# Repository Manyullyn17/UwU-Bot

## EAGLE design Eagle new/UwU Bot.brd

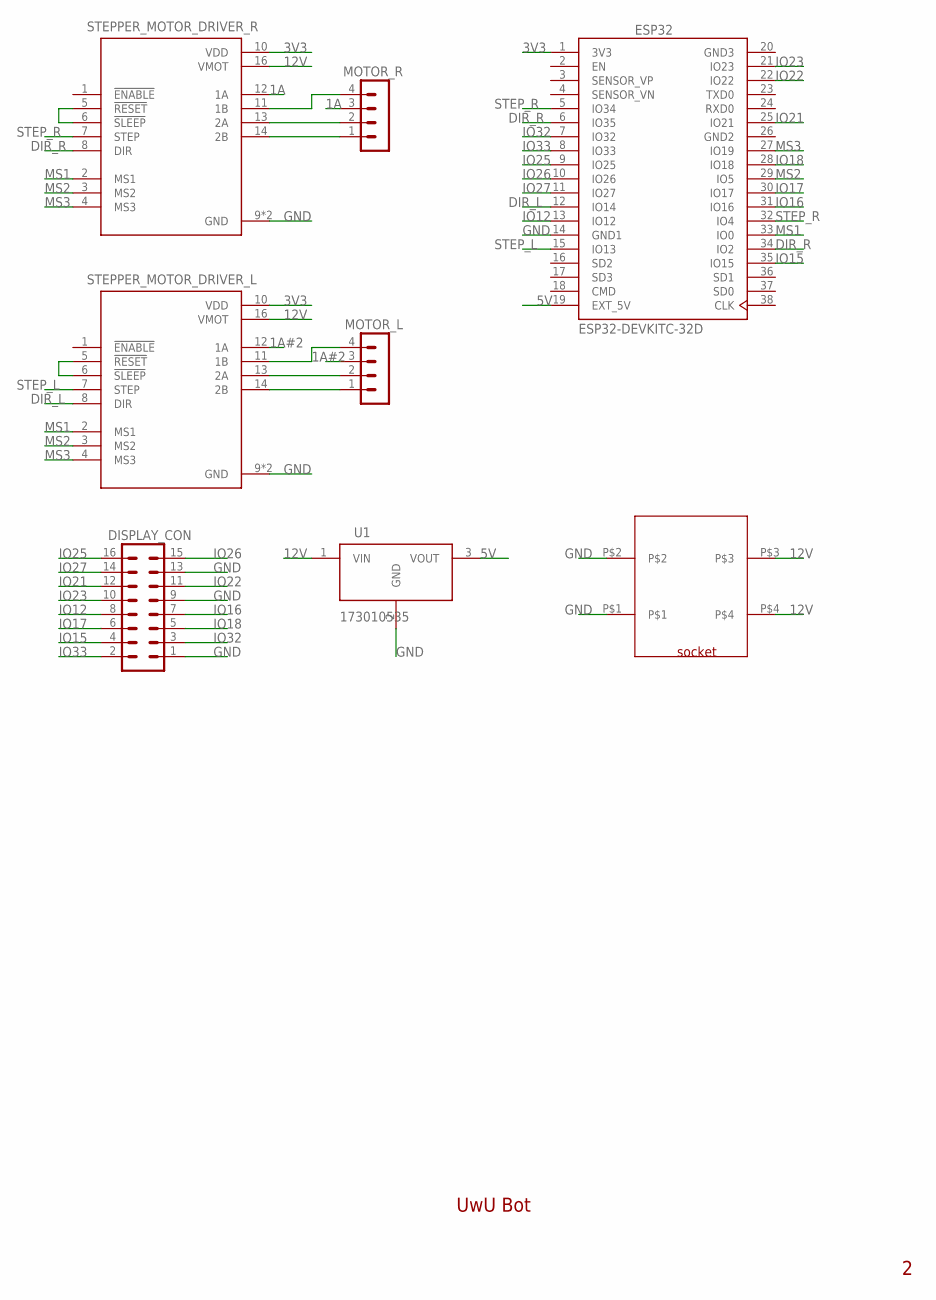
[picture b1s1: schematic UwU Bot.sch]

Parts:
DISPLAY_CON: MA08-2
ESP32: ESP32-DEVKITC-32D; MODULE_ESP32-DEVKITC-32D
MOTOR_L: MA04-1
MOTOR_R: MA04-1
STEPPER_MOTOR_DRIVER_L: A4988_STEPPER_MOTOR_DRIVER; MODULE_A4988_STEPPER_MOTOR_DRIVER_CARRIER_BLACK
STEPPER_MOTOR_DRIVER_R: A4988_STEPPER_MOTOR_DRIVER; MODULE_A4988_STEPPER_MOTOR_DRIVER_CARRIER_BLACK
U1: 173010535
U$1: BUCHSEDC; BUCHSE

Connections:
1A: MOTOR_R.3, STEPPER_MOTOR_DRIVER_R.12 (1A)
1A#2: MOTOR_L.3, STEPPER_MOTOR_DRIVER_L.12 (1A)
3V3: ESP32.1 (3V3), STEPPER_MOTOR_DRIVER_L.10 (VDD), STEPPER_MOTOR_DRIVER_R.10 (VDD)
5V: ESP32.19 (EXT_5V), U1.3 (VOUT)
12V: STEPPER_MOTOR_DRIVER_L.16 (VMOT), STEPPER_MOTOR_DRIVER_R.16 (VMOT), U1.1 (VIN), U$1.P$3, U$1.P$4
DIR_L: ESP32.12 (IO14), STEPPER_MOTOR_DRIVER_L.8 (DIR)
DIR_R: ESP32.6 (IO35), ESP32.34 (IO2), STEPPER_MOTOR_DRIVER_R.8 (DIR)
GND: DISPLAY_CON.1, DISPLAY_CON.9, DISPLAY_CON.13, ESP32.14 (GND1), STEPPER_MOTOR_DRIVER_L.9 (GND), STEPPER_MOTOR_DRIVER_L.15 (GND), STEPPER_MOTOR_DRIVER_R.9 (GND), STEPPER_MOTOR_DRIVER_R.15 (GND), U1.2 (GND), U$1.P$1, U$1.P$2
GND2: ESP32.26 (GND2)
GND3: ESP32.20 (GND3)
IO12: DISPLAY_CON.8, ESP32.13 (IO12)
IO15: DISPLAY_CON.4, ESP32.35 (IO15)
IO16: DISPLAY_CON.7, ESP32.31 (IO16)
IO17: DISPLAY_CON.6, ESP32.30 (IO17)
IO18: DISPLAY_CON.5, ESP32.28 (IO18)
IO21: DISPLAY_CON.12, ESP32.25 (IO21)
IO22: DISPLAY_CON.11, ESP32.22 (IO22)
IO23: DISPLAY_CON.10, ESP32.21 (IO23)
IO25: DISPLAY_CON.16, ESP32.9 (IO25)
IO26: DISPLAY_CON.15, ESP32.10 (IO26)
IO27: DISPLAY_CON.14, ESP32.11 (IO27)
IO32: DISPLAY_CON.3, ESP32.7 (IO32)
IO33: DISPLAY_CON.2, ESP32.8 (IO33)
MS1: ESP32.33 (IO0), STEPPER_MOTOR_DRIVER_L.2 (MS1), STEPPER_MOTOR_DRIVER_R.2 (MS1)
MS2: ESP32.29 (IO5), STEPPER_MOTOR_DRIVER_L.3 (MS2), STEPPER_MOTOR_DRIVER_R.3 (MS2)
MS3: ESP32.27 (IO19), STEPPER_MOTOR_DRIVER_L.4 (MS3), STEPPER_MOTOR_DRIVER_R.4 (MS3)
unnamed: MOTOR_R.4, STEPPER_MOTOR_DRIVER_R.11 (1B)
unnamed: STEPPER_MOTOR_DRIVER_R.5 (!RESET), STEPPER_MOTOR_DRIVER_R.6 (!SLEEP)
unnamed: STEPPER_MOTOR_DRIVER_L.5 (!RESET), STEPPER_MOTOR_DRIVER_L.6 (!SLEEP)
unnamed: MOTOR_L.4, STEPPER_MOTOR_DRIVER_L.11 (1B)
unnamed: MOTOR_L.2, STEPPER_MOTOR_DRIVER_L.13 (2A)
unnamed: MOTOR_L.1, STEPPER_MOTOR_DRIVER_L.14 (2B)
unnamed: MOTOR_R.1, STEPPER_MOTOR_DRIVER_R.14 (2B)
unnamed: MOTOR_R.2, STEPPER_MOTOR_DRIVER_R.13 (2A)
STEP_L: ESP32.15 (IO13), STEPPER_MOTOR_DRIVER_L.7 (STEP)
STEP_R: ESP32.5 (IO34), ESP32.32 (IO4), STEPPER_MOTOR_DRIVER_R.7 (STEP)

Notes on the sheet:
UwU Bot

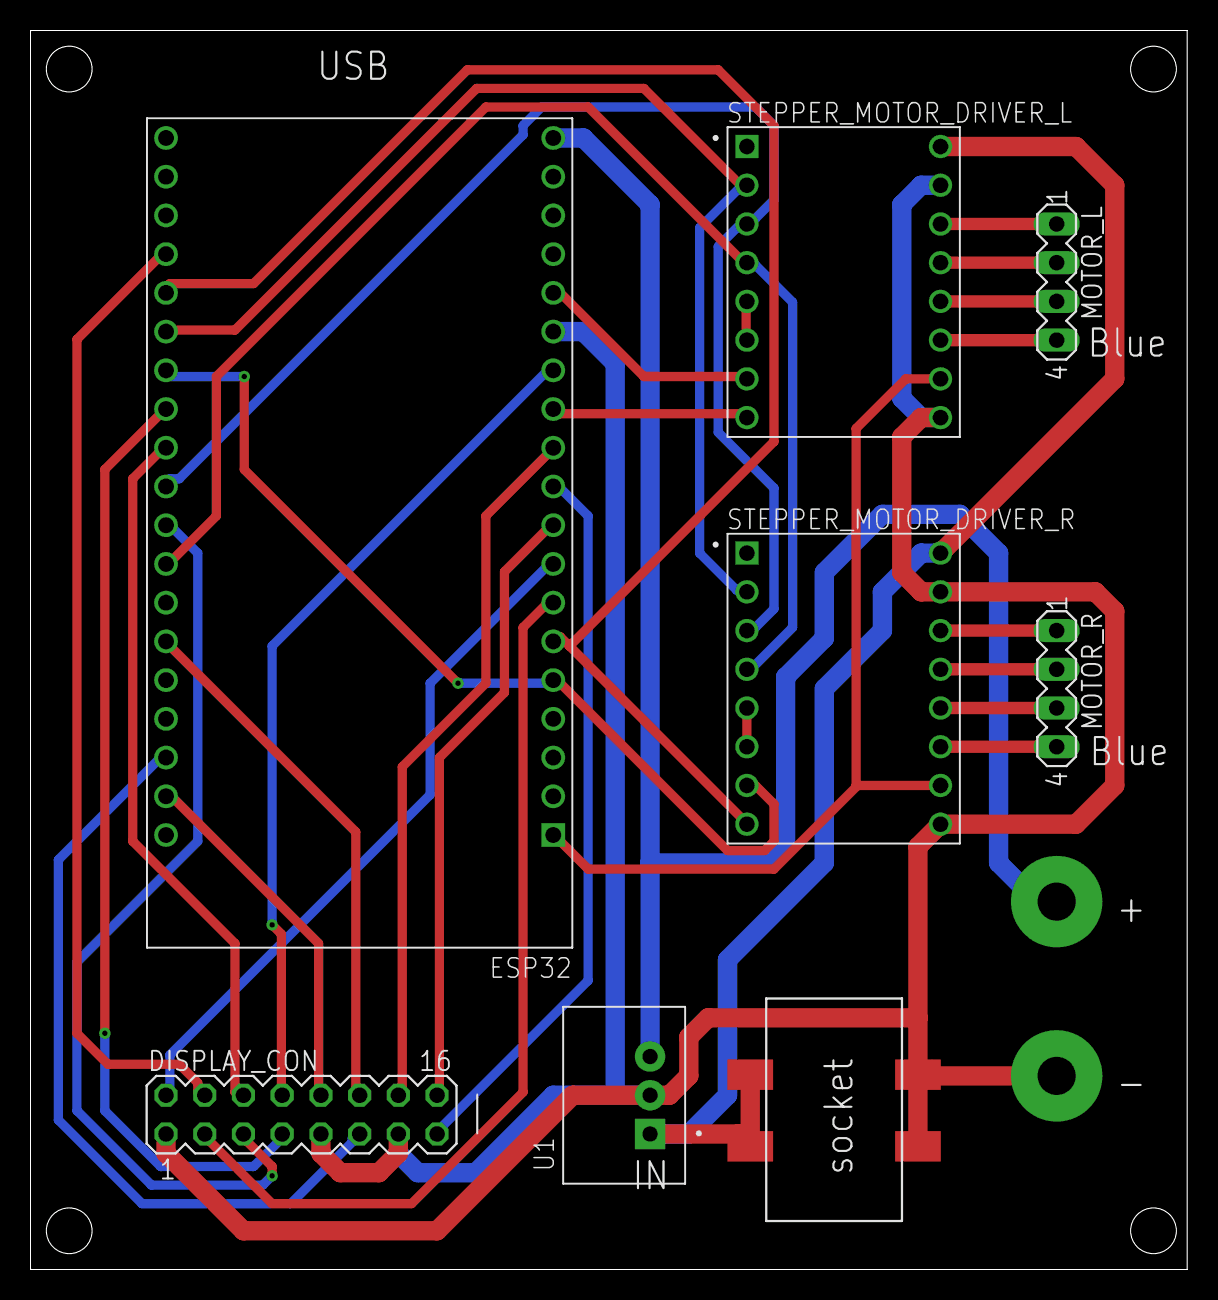
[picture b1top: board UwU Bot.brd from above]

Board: 2 copper layers, 75.9 x 81.3 mm, 8 parts (0 on the bottom side), 34 nets.

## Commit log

2023-03-15 added .gitignore
2023-03-16 added Eagle, ESP32 Datasheet and faces
2023-03-16 Bluetooth Library working
2023-03-23 fixed bluetooth
2023-03-29 added hires faces and fully featured esp32 program
2023-03-30 UwU-Bot_Control finally works
2023-03-30 fixed MS1 Pin number and renamed UwU-Bot-App Folder
2023-04-05 added Pictures
2023-04-20 updated Eagle
2023-04-20 updated android and arduino
2023-04-20 added arduino code with new display lib and cleaned up old code
2023-04-21 fixed and improved EAGLE Layout
2023-04-21 moved all pictures in pictures folder
2023-04-21 cleanup and fixed hole size
2023-04-26 added Document
2023-05-15 added new pictures, reorganized folder structure and removed debugging from newest version of code
2023-05-15 added Overview for Presentation
2023-05-15 fixed formatting
2023-05-15 changed Linebreak
2023-05-15 added Steering and more to Wheels
2023-05-16 renamed Logo files and changes in overview.md
2023-05-22 added pictures and updated doc and pptx
